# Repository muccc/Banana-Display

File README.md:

# Banana-Display
Adapter Board Banana PI LVDS FPC to 30 Pin DF14 connector and Backlight connection

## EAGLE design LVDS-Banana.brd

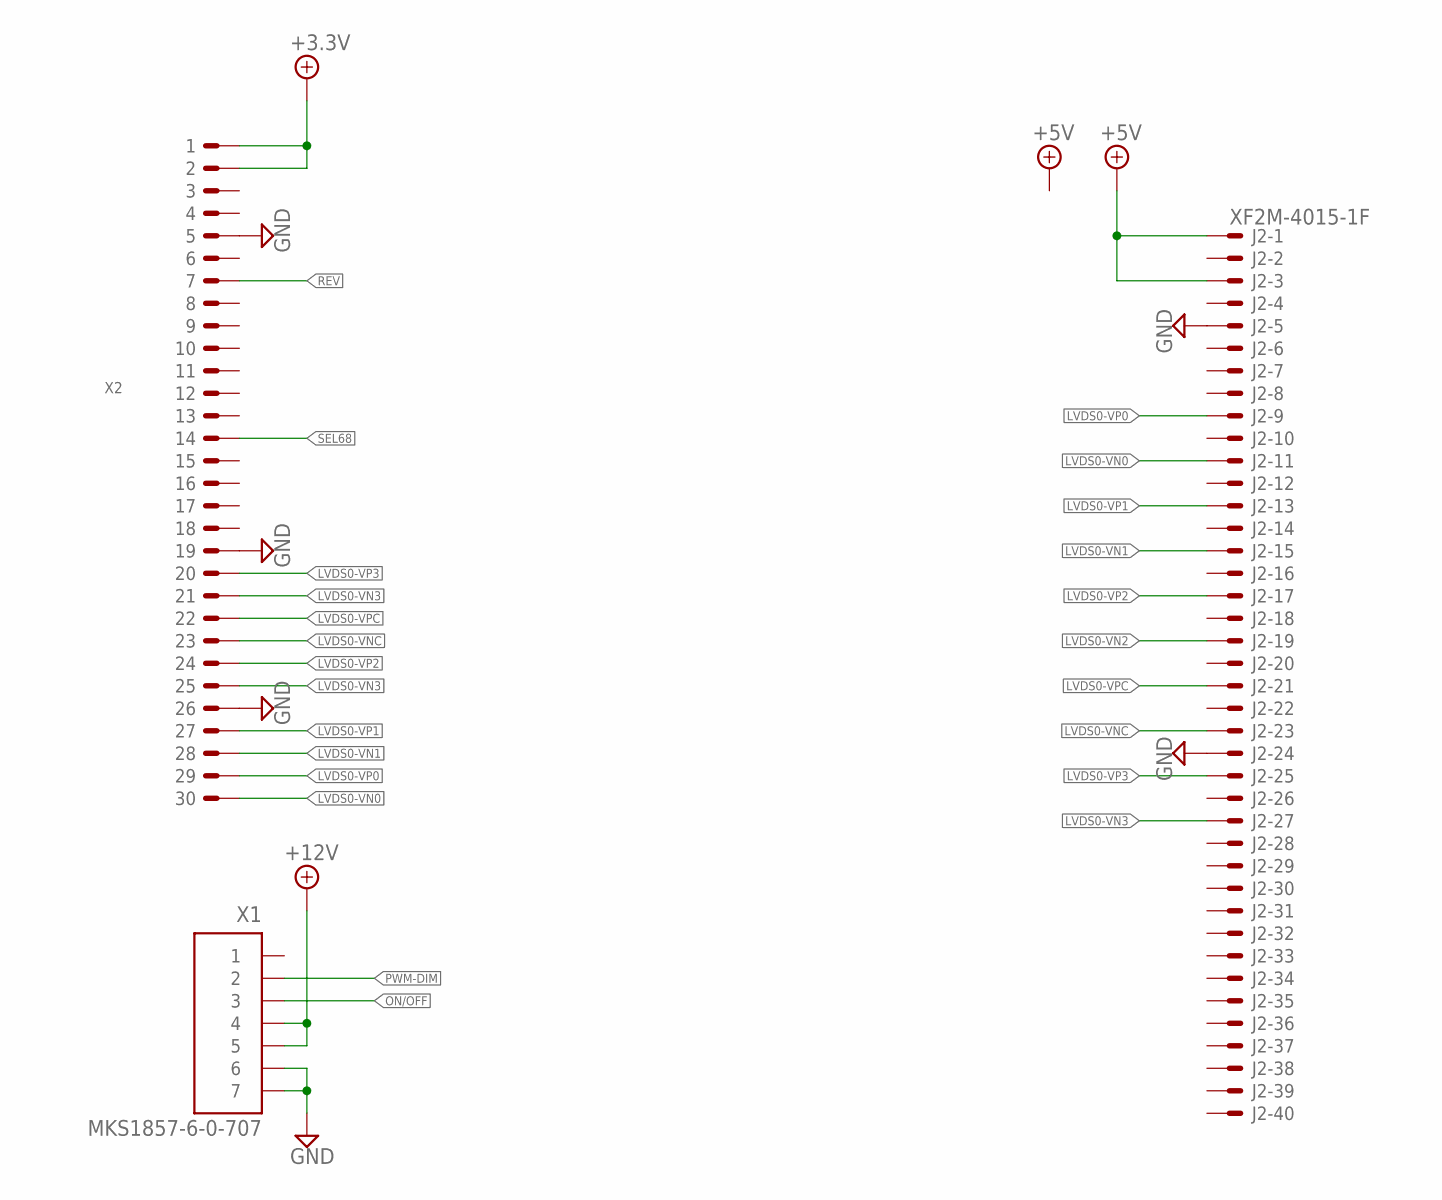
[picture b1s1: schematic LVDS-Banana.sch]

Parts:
J2: XF2M-4015-1F
X1: MKS1857-6-0-707
X2: DF14-30P-1.25H; DF14-30

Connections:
+3.3V: X2.1, X2.2
+5V: J2.1 (MSV), J2.3 (MS)
+12V: X1.4, X1.5
GND: J2.5 (MS), J2.24 (MS), X1.6, X1.7, X2.5, X2.19, X2.26
LVDS0-VN0: J2.11 (MS), X2.30
LVDS0-VN1: J2.15 (MS), X2.28
LVDS0-VN2: J2.19 (MS)
LVDS0-VN3: J2.27 (MS), X2.21, X2.25
LVDS0-VNC: J2.23 (MS), X2.23
LVDS0-VP0: J2.9 (MS), X2.29
LVDS0-VP1: J2.13 (MS), X2.27
LVDS0-VP2: J2.17 (MS), X2.24
LVDS0-VP3: J2.25 (MS), X2.20
LVDS0-VPC: J2.21 (MS), X2.22
ON/OFF: X1.3
PWM-DIM: X1.2
REV: X2.7
SEL68: X2.14

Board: 2 copper layers, 3 parts (0 on the bottom side), 13 nets, no tracks yet.

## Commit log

2015-09-04 Erster Entwurf, Spannungsregler und Steuerleitung fehlen noch und Pinouts und Datenblätter fehlen noch, bitte Display Datenblatt committen
